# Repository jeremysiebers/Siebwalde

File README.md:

# Siebwalde-Source
Siebwalde project

This project is dedicated for the ModelTrain Yard of Siebwalde: 
- https://www.youtube.com/c/SiebersOrg
- http://www.siebers.org/index.html
- https://www.youtube.com/channel/UCRJYaY8l7wVBrel3Bn0nD2Q/videos?view_as=subscriber

It contains sources for:

Windows Application (C#)

- Siebwalde_Application     --> C# main App to control all

uCOntrollers (C):

- FiddleYard                --> Embedded ethernet uController, controlling the FiddleYard PIC18F97j60

- ServoController.X         --> Embedded uController for RC servo driving

- TrackAmplifier4.X         --> development of track amplifiers; 1 PIC per amplifier (final setup with PIC18F25K40)(PetitModbus)*

- TrackBackplane2.X         --> development of track backplane slave; track amplifier slave select slave for initialization (final setup with PIC18F25K40)(PetitModbus)*

- TrackController5.X        --> development of track controller; PIC32MZ2048EFH144 Ethernet Target + ModBus Master(build upon PetitModbus)*

PCB Files (KiCad):

- KiCad                     --> All Siebwalde related KiCad (PCB) designs

*PetitModbus derived from https://github.com/FxDev/PetitModbus

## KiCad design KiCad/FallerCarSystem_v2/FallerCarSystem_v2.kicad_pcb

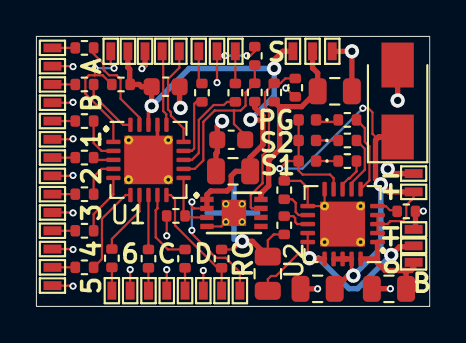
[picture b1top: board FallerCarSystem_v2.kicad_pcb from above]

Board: 2 copper layers, 21.8 x 15.0 mm, 77 parts (0 on the bottom side), 46 nets.

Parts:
C1, C2: 0.1uF; C_0603_1608Metric
C3, C5, C6, C7: 4.7uF; C_0805_2012Metric
C4: 10uF; C_0805_2012Metric
D1: SMAJ5.0A/AC; D_SMA
D2, D3, D4: LED; LED_0402_1005Metric
J1, J2, J3, J4, J5, J6, J7, J8, J9, J10, J11, J12, J13, J14, J15, J16, J17, J18, J19, J20, J21, J22, J23, J24, J25, J26, J27, J28, J29, J30, J31, J32, J33, J34, J35, J36, J37, J38: Conn_01x01_Male; TestPoint_Pad_0.5x1.0mm
R1, R2, R9, R15: 4.7k; R_0402_1005Metric
R3: 4k7; R_0402_1005Metric
R4: 18k; R_0402_1005Metric
R5, R6: 200E; R_0402_1005Metric
R7: 220k; R_0402_1005Metric
R8: 10k; R_0402_1005Metric
R10: 47k; R_0402_1005Metric
R11: 22k; R_0402_1005Metric
R12, R13, R14, R16, R17, R18, R19, R20, R21, R22, R23, R24, R25: 470E; R_0402_1005Metric
U1: PIC16F15345-I_GZ-MCU_Microchip_PIC16; QFN-20-1EP_4x4mm_P0.5mm_EP2.7x2.7mm_ThermalVias
U2: MCP73871-2AA; QFN-20-1EP_4x4mm_P0.5mm_EP2.5x2.5mm_ThermalVias
U3: MCP1725-ADJE_MC_DFN-8-Regulator_Linear; DFN-8-1EP_3x2mm_P0.5mm_EP1.36x1.46mm_ThermalVias

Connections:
+3V8: C1.1, C3.1, J5.1, J12.1, J13.1, R1.2, R3.2, U1.18, U3.1, U3.2
+5V: C4.1, D1.1, D2.2, D3.2, D4.2, J15.1, U2.2, U2.3, U2.4, U2.9, U2.17, U2.18, U2.19
/PG: R12.1, U2.6
/STAT1: R13.1, U2.8
/STAT2: R14.1, U2.7
BATT: C6.1, J17.1, U2.14, U2.15, U2.16
EnMOT: R9.2, U1.11, U3.3
GND: C1.2, C2.2, C3.2, C4.2, C5.2, C6.2, C7.2, D1.2, J3.1, J6.1, J10.1, J16.1, J18.1, J20.1, J22.1, J24.1, J26.1, J28.1, J30.1, J32.1, J34.1, J36.1, J38.1, R2.1, R4.1, R7.1, R8.1, R9.1, R11.1, R15.1, U1.17, U1.21, U2.10, U2.11, U2.21, U3.4, U3.9
ICSPCLK: J8.1, U1.15
ICSPDATA: J7.1, U1.16
LEDA: R23.2, U1.19
LEDB: R22.2, U1.20
LEDC: R25.2, U1.8
LEDD: R24.2, U1.9
MOTOR+: C5.1, J9.1, R10.2, U3.8
unnamed: D2.1, R12.2
unnamed: D3.1, R13.2
unnamed: D4.1, R14.2
unnamed: J19.1, R16.1
unnamed: J21.1, R17.1
unnamed: J23.1, R18.1
unnamed: J25.1, R19.1
unnamed: J27.1, R20.1
unnamed: J29.1, R21.1
unnamed: J31.1, R22.1
unnamed: J33.1, R23.1
unnamed: J35.1, R24.1
unnamed: J37.1, R25.1
unnamed: R4.2, U2.13
unnamed: R5.2, U1.13
unnamed: R6.2, U1.14
unnamed: R7.2, U2.12
unnamed: R8.2, U2.5
unnamed: R10.1, R11.2, U3.7
PWM1: R16.2, U1.2
PWM2: R17.2, U1.3
PWM3: R18.2, U1.4
PWM4: R19.2, U1.5
PWM5: R20.2, U1.6
PWM6: R21.2, U1.7
RCS_IN: J14.1, R15.2, U1.10
SWONOFF_OUT: C7.1, J11.1, U2.1, U2.20
UART_RX: J2.1, R6.1
UART_TX: J1.1, R5.1
Vbatt: C2.1, R1.1, R2.2, U1.12
Vpp: J4.1, R3.1, U1.1

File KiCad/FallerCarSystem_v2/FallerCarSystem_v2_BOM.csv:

Comment,Designator,Footprint
0.1uF,"C1, C2",Capacitor_SMD:C_0603_1608Metric
4.7uF,"C3, C5, C6, C7",Capacitor_SMD:C_0805_2012Metric
10uF,C4,Capacitor_SMD:C_0805_2012Metric
SMAJ5.0A/AC,D1,Diode_SMD:D_SMA
Everlight Elec 16-213SYGC/S530-E3/TR8,"D2, D4",LED_SMD:LED_0402_1005Metric
Everlight Elec 16-213/SDRC/S530-A3/TR8,D3,LED_SMD:LED_0402_1005Metric
4.7k,"R1, R2, R3, R9, R15",Resistor_SMD:R_0402_1005Metric
18k,R4,Resistor_SMD:R_0402_1005Metric
200,"R5, R6",Resistor_SMD:R_0402_1005Metric
220k,R7,Resistor_SMD:R_0402_1005Metric
10k,R8,Resistor_SMD:R_0402_1005Metric
47k,R10,Resistor_SMD:R_0402_1005Metric
22k,R11,Resistor_SMD:R_0402_1005Metric
470,"R12, R13, R14",Resistor_SMD:R_0402_1005Metric
150,"R16, R17, R18, R19, R20, R21, R22, R23, R24, R25",Resistor_SMD:R_0402_1005Metric
PIC16F15345-I_GZ-MCU_Microchip_PIC16_UQFN_20_4x4,U1,Package_DFN_QFN:QFN-20-1EP_4x4mm_P0.5mm_EP2.7x2.7mm_ThermalVias
MCP73871-2AA_VQFN_20_4x4,U2,Package_DFN_QFN:QFN-20-1EP_4x4mm_P0.5mm_EP2.5x2.5mm_ThermalVias
MCP1725-ADJE_MC_DFN-8-Regulator_Linear,U3,Package_DFN_QFN:DFN-8-1EP_3x2mm_P0.5mm_EP1.36x1.46mm_ThermalVias

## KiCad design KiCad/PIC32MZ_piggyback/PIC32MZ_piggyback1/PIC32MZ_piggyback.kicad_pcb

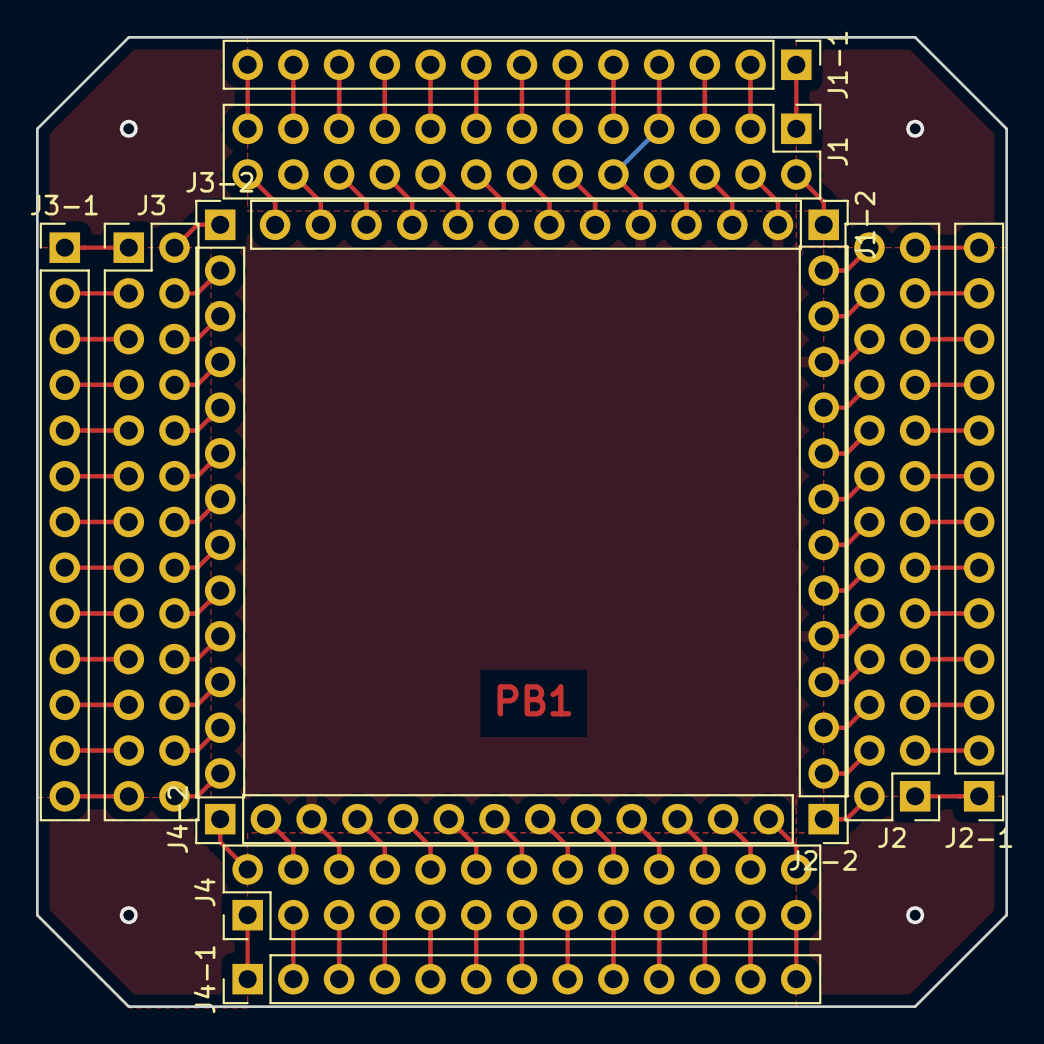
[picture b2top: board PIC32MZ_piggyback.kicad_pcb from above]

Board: 2 copper layers, 53.8 x 53.8 mm, 12 parts (0 on the bottom side), 84 nets.

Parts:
J1, J2, J3, J4: Conn_02x13_Odd_Even; PinHeader_2x13_P2.54mm_Vertical
J1-1, J1-2, J2-1, J2-2, J3-1, J3-2, J4-1, J4-2: Conn_01x13_Male; PinHeader_1x13_P2.54mm_Vertical

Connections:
/GND: J1.4, J1.7, J1.10, J1-1.4, J1-2.2, J1-2.5, J2.10, J2.15, J2.22, J2-1.8, J2-2.5, J2-2.11, J3.15, J3-1.8, J4.6, J4.11, J4.15, J4-1.6, J4-1.8, J4-2.3
/LED1: J3.3, J3-1.2, J4.9, J4-1.5
/LED2: J3.5, J3-1.3, J4.10, J4-2.5
/MCLR: J3.13, J3-1.7
/MCU_MISO: J4.7, J4-1.4
/MCU_MOSI: J4.18, J4-2.9
/MCU_SCK: J4.16, J4-2.8
/RA0: J1.17, J1-1.9
/RA1: J3.18, J3-2.9
/RA2: J4.13, J4-1.7
/RA3: J4.20, J4-2.10
/RA4: J4.19, J4-1.10
/RA5: J4.22, J4-2.11
/RA9: J3.7, J3-1.4
/RA10: J3.12, J3-2.6
/RA14: J4.21, J4-1.11
/RA15: J4.24, J4-2.12
/RB0: J1.25, J1-1.13
/RB1: J1.26, J1-2.13
/RB2: J1.23, J1-1.12
/RB3: J1.24, J1-2.12
/RB4: J1.21, J1-1.11
/RB5: J1.22, J1-2.11
/RB6: J2.17, J2-1.9
/RB7: J2.7, J2-1.4
/RB8: J3.9, J3-1.5
/RB9: J3.14, J3-2.7
/RB10: J3.11, J3-1.6
/RB11: J3.16, J3-2.8
/RB12: J3.19, J3-1.10
/RB13: J3.22, J3-2.11
/RB14: J3.21, J3-1.11
/RB15: J3.24, J3-2.12
/RC1: J1.8, J1-2.4
/RC2: J1.9, J1-1.5
/RC3: J1.12, J1-2.6
/RC4: J1.13, J1-1.7
/RD0: J4.25, J4-1.13
/RD1: J2.1, J2-1.1
/RD2: J2.2, J2-2.1
/RD3: J2.3, J2-1.2
/RD4: J2.11, J2-1.6
/RD5: J2.8, J2-2.4
/RD7: J2.14, J2-2.7
/RD9: J4.26, J4-2.13
/RD10: J4.23, J4-1.12
/RD12: J2.5, J2-1.3
/RD13: J2.4, J2-2.2
/RD14: J3.23, J3-1.12
/RE0: J2.18, J2-2.9
/RE2: J2.21, J2-1.11
/RE3: J2.26, J2-2.13
/RE7: J1.5, J1-1.3
/RE8: J1.20, J1-2.10
/RE9: J1.19, J1-1.10
/RF0: J2.16, J2-2.8
/RF1: J2.13, J2-1.7
/RF3: J4.14, J4-2.7
/RF4: J3.25, J3-1.13
/RF5: J3.26, J3-2.13
/RF12: J3.20, J3-2.10
/RG6: J1.14, J1-2.7
/RG7: J1.15, J1-1.8
/RG8: J1.16, J1-2.8
/RG9: J1.18, J1-2.9
/RG12: J2.19, J2-1.10
/RG14: J2.20, J2-2.10
/RXN: J2.23, J2-1.12
/RXP: J2.24, J2-2.12
/TXN: J1.2, J1-2.1
/TXP: J1.3, J1-1.2
/VCC: J1.1, J1.6, J1.11, J1-1.1, J1-1.6, J1-2.3, J2.9, J2.12, J2.25, J2-1.5, J2-1.13, J2-2.6, J3.17, J3-1.9, J4.4, J4.5, J4.12, J4-1.3, J4-2.2, J4-2.6
unnamed: J2.6, J2-2.3
unnamed: J3.1, J3-1.1
unnamed: J3.2, J3-2.1
unnamed: J3.4, J3-2.2
unnamed: J3.6, J3-2.3
unnamed: J3.8, J3-2.4
unnamed: J3.10, J3-2.5
unnamed: J4.1, J4-1.1
unnamed: J4.3, J4-1.2
unnamed: J4.17, J4-1.9
unnamed: J4.2, J4-2.1
unnamed: J4.8, J4-2.4

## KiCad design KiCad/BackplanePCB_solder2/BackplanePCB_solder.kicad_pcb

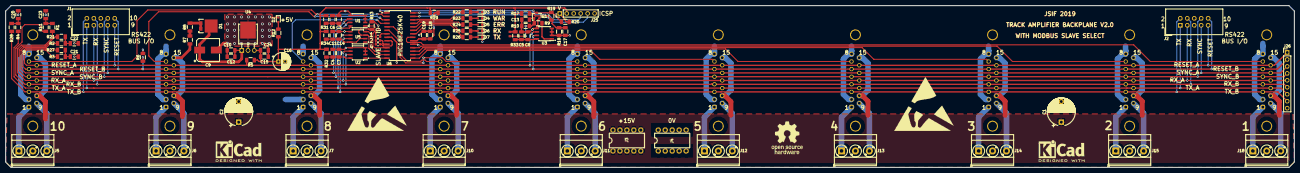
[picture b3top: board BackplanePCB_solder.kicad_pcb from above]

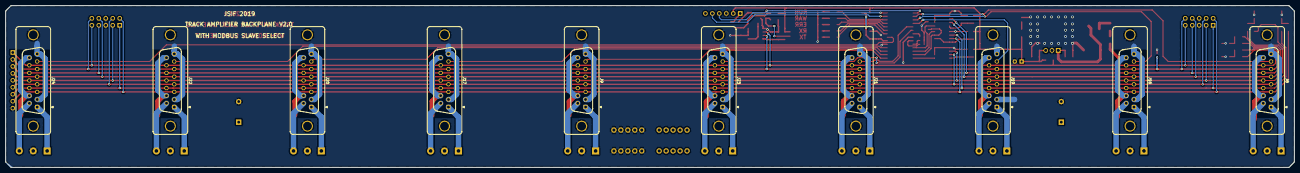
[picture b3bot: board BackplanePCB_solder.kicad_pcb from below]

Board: 2 copper layers, 470.0 x 59.0 mm, 98 parts (10 on the bottom side), 78 nets.

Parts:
C1, C2: 470u; CP_Radial_D10.0mm_P7.50mm
C3, C4, C5, C10, C11, C18, C24: 4.7u; C_1206_3216Metric
C6, C7, C8, C12, C13, C14, C15, C17, C19, C20, C21, C22, C23: 100n; C_1206_3216Metric
C9: 220u; CP_Elec_8x10.5
C16: 220u; CP_Radial_D6.3mm_P2.50mm
D1: D_Schottky_AAK; TO-277A
D2, D3: LED GR RUN; LED_0.8x0.8
D4: LED YE WAR; LED_0.8x0.8
D5: LED RD ERR; LED_0.8x0.8
D6: LED GR RX; LED_0.8x0.8
D7: LED GR TX; LED_0.8x0.8
J1, J2: Conn_02x05_Odd_Even; IDC-Header_2x05_P2.54mm_Vertical
J3: PowerBug+15V; DIP-10_W7.62mm
J4: PowerBug_GND; DIP-10_W7.62mm
J5, J6, J7, J10, J11, J12, J13, J14, J15, J18: Conn_01x03; TerminalBlock_Phoenix_MKDS-3-3-5.08_1x03_P5.08mm_Horizontal
J8, J9, J16, J17, J19, J20, J21, J22, J23, J24: DB15_Female_MountingHoles; DSUB-15_Female_Vertical_P2.77x2.84mm_MountingHoles
J25: Conn_01x06; PinHeader_1x06_P2.54mm_Vertical
J26: Conn_01x09; PinHeader_1x09_P2.54mm_Vertical
Q1: NTR5103NT1G; SOT-23
R1, R2, R3, R4, R11, R21, R27, R28: 60E; R_1206_3216Metric
R5, R6: 2k; R_1206_3216Metric
R7, R8: 10E; R_1206_3216Metric
R9, R13: 1k; R_1206_3216Metric
R10, R17: 10k; R_1206_3216Metric
R12, R22, R23, R24, R25, R26: 300E; R_1206_3216Metric
R14, R15, R16: R; R_0603_1608Metric
R18: 110k; R_1206_3216Metric
R19, R20: 470; R_1206_3216Metric
R29, R31, R32, R33, R34: 0E; R_1206_3216Metric
R30: NP; R_0603_1608Metric
U1, U2, U3, U5: ST485EBDR; SOIC-8_3.9x4.9mm_P1.27mm
U4: L78M05CDT-1-TO-251-3; TO-251-3-1EP_Horizontal_TabDown
U6: PIC16F18854-SO; SOIC-28W_7.5x17.9mm_P1.27mm

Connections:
+5V: C15.1, C16.1, C24.1, J25.2, R5.1, R12.1, R17.2, R29.1, R30.1, R31.1, R32.1, R33.1, R34.1, U4.3
+15V: C1.1, C2.1, J3.1, J3.2, J3.3, J3.4, J3.5, J3.6, J3.7, J3.8, J3.9, J3.10, J8.10, J8.15, J9.10, J9.15, J16.10, J16.15, J17.10, J17.15, J19.10, J19.15, J20.10, J20.15, J21.10, J21.15, J22.10, J22.15, J23.10, J23.15, J24.10, J24.15, R7.1
/PWMO1_1: J5.3, J8.9
/PWMO1_2: J6.3, J16.9
/PWMO1_3: J7.3, J19.9
/PWMO1_4: J10.3, J21.9
/PWMO1_5: J11.3, J23.9
/PWMO1_6: J9.9, J12.3
/PWMO1_7: J13.3, J17.9
/PWMO1_8: J14.3, J20.9
/PWMO1_9: J15.3, J22.9
/PWMO1_10: J18.3, J24.9
/PWMO2_1: J5.1, J8.1
/PWMO2_2: J6.1, J16.1
/PWMO2_3: J7.1, J19.1
/PWMO2_4: J10.1, J21.1
/PWMO2_5: J11.1, J23.1
/PWMO2_6: J9.1, J12.1
/PWMO2_7: J13.1, J17.1
/PWMO2_8: J14.1, J20.1
/PWMO2_9: J15.1, J22.1
/PWMO2_10: J18.1, J24.1
GND: C1.2, C2.2, C3.2, C4.2, C5.2, C6.2, C7.2, C8.2, C9.2, C10.2, C11.2, C12.2, C13.2, C14.2, C15.2, C16.2, C17.2, C18.2, C19.2, C20.2, C21.2, C22.2, C23.2, C24.2, D2.1, D3.1, D4.1, D5.1, D6.1, D7.1, J1.5, J1.6, J2.5, J2.6, J4.1, J4.2, J4.3, J4.4, J4.5, J4.6, J4.7, J4.8, J4.9, J4.10, J5.2, J6.2, J7.2, J8.0, J8.2, J8.8, J9.0, J9.2, J9.8, J10.2, J11.2, J12.2, J13.2, J14.2, J15.2, J16.0, J16.2, J16.8, J17.0, J17.2, J17.8, J18.2, J19.0, J19.2, J19.8, J20.0, J20.2, J20.8, J21.0, J21.2, J21.8, J22.0, J22.2, J22.8, J23.0, J23.2, J23.8, J24.0, J24.2, J24.8, J25.3, J26.9, Q1.2, R6.1, R10.2, R13.1, R14.2, R15.2, R16.2, R18.1, U1.2, U1.3, U1.4, U1.5, U2.2, U2.3, U2.4, U2.5, U3.2, U3.3, U3.4, U3.5, U4.2, U4.4, U5.5, U6.8, U6.19
ICSPCLK: J25.5, U6.27
ICSPDAT: J25.4, U6.28
ID_1: J24.7, U6.21
ID_2: J22.7, U6.18
ID_3: J20.7, U6.17
ID_4: J17.7, U6.16
ID_5: J9.7, U6.15
ID_6: J23.7, U6.6
ID_7: J21.7, U6.5
ID_8: J19.7, U6.4
ID_9: J16.7, U6.3
ID_10: J8.7, U6.2
unnamed: C3.1, C6.1, R31.2, U1.8
unnamed: C4.1, C7.1, R32.2, U2.8
unnamed: C5.1, C8.1, R33.2, U3.8
unnamed: C9.1, C10.1, C12.1, D1.3, U4.1
unnamed: C11.1, C14.1, R34.2, U5.2, U5.8
unnamed: C13.1, Q1.1, R9.2, R10.1, R30.2
unnamed: C17.1, R17.1, R18.2, R19.1
unnamed: C18.1, C19.1, R29.2, U6.20
unnamed: C20.1, R4.1, R28.2
unnamed: C21.1, R3.1, R27.2
unnamed: C22.1, R2.1, R21.2
unnamed: C23.1, R1.1, R11.2
unnamed: D1.1, D1.2, R8.2
unnamed: D2.2, R12.2
unnamed: D3.2, R22.2
unnamed: D4.2, R23.2
unnamed: D5.2, R24.2
unnamed: D6.2, R25.2
unnamed: D7.2, R26.2
unnamed: R7.2, R8.1
unnamed: R9.1, U3.1
unnamed: R14.1, U6.7
unnamed: R15.1, U6.10
unnamed: R16.1, U6.9
unnamed: R22.1, U6.26
unnamed: R23.1, U6.25
unnamed: R24.1, U6.24
unnamed: R25.1, U6.23
unnamed: R26.1, U6.22
RESET_A: J1.9, J2.9, J8.14, J9.14, J16.14, J17.14, J19.14, J20.14, J21.14, J22.14, J23.14, J24.14, J26.1, R3.2, R5.2, U3.6
RESET_B: J1.10, J2.10, J8.6, J9.6, J16.6, J17.6, J19.6, J20.6, J21.6, J22.6, J23.6, J24.6, J26.2, R6.2, R27.1, U3.7
RST: Q1.3, R19.2, R20.1, U6.1
RX: U2.1, U6.14
RX_A: J1.3, J2.3, J8.12, J9.12, J16.12, J17.12, J19.12, J20.12, J21.12, J22.12, J23.12, J24.12, J26.5, R1.2, U2.6
RX_B: J1.4, J2.4, J8.4, J9.4, J16.4, J17.4, J19.4, J20.4, J21.4, J22.4, J23.4, J24.4, J26.6, R11.1, U2.7
SYNC: U1.1, U6.11
SYNC_A: J1.7, J2.7, J8.13, J9.13, J16.13, J17.13, J19.13, J20.13, J21.13, J22.13, J23.13, J24.13, J26.3, R2.2, U1.6
SYNC_B: J1.8, J2.8, J8.5, J9.5, J16.5, J17.5, J19.5, J20.5, J21.5, J22.5, J23.5, J24.5, J26.4, R21.1, U1.7
TX: U5.4, U6.12
TX_A: J1.1, J2.1, J8.11, J9.11, J16.11, J17.11, J19.11, J20.11, J21.11, J22.11, J23.11, J24.11, J26.7, R4.2, U5.6
TX_B: J1.2, J2.2, J8.3, J9.3, J16.3, J17.3, J19.3, J20.3, J21.3, J22.3, J23.3, J24.3, J26.8, R28.1, U5.7
TX_ENA: R13.2, U5.3, U6.13
VPP: J25.1, R20.2

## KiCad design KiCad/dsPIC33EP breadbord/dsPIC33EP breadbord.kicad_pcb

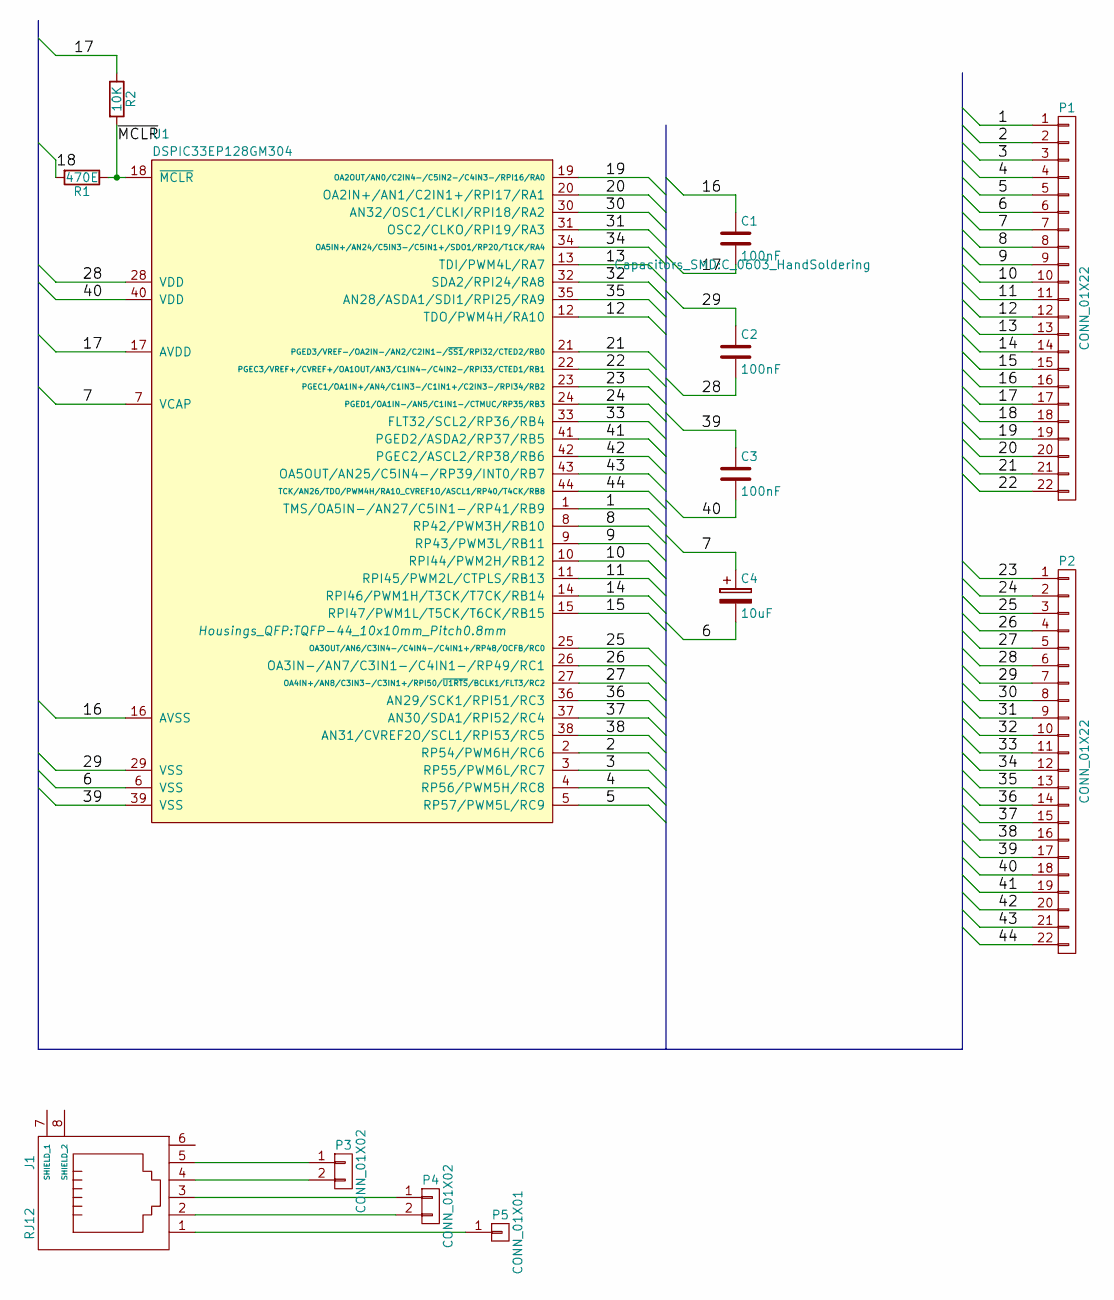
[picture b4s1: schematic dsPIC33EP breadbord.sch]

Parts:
C1, C2, C3: 100nF; C_0603_HandSoldering
C4: 10uF; TantalC_SizeA_EIA-3216_HandSoldering
J1: RJ12; RJ12_E
P1, P2: CONN_01X22; Pin_Header_Straight_1x22
P3, P4: CONN_01X02; Pin_Header_Straight_1x02
P5: CONN_01X01; Pin_Header_Straight_1x01
R1: 470E; R_0603_HandSoldering
R2: 10K; R_0603_HandSoldering
U1: DSPIC33EP128GM304; TQFP-44_10x10mm_Pitch0.8mm

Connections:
/1: P1.1, U1.1 (TMS/OA5IN-/AN27/C5IN1-/RP41/RB9)
/2: P1.2, U1.2 (RP54/PWM6H/RC6)
/3: P1.3, U1.3 (RP55/PWM6L/RC7)
/4: P1.4, U1.4 (RP56/PWM5H/RC8)
/5: P1.5, U1.5 (RP57/PWM5L/RC9)
/6: C4.2, P1.6, U1.6 (VSS)
/7: C4.1, P1.7, U1.7 (VCAP)
/8: P1.8, U1.8 (RP42/PWM3H/RB10)
/9: P1.9, U1.9 (RP43/PWM3L/RB11)
/10: P1.10, U1.10 (RPI44/PWM2H/RB12)
/11: P1.11, U1.11 (RPI45/PWM2L/CTPLS/RB13)
/12: P1.12, U1.12 (TDO/PWM4H/RA10)
/13: P1.13, U1.13 (TDI/PWM4L/RA7)
/14: P1.14, U1.14 (RPI46/PWM1H/T3CK/T7CK/RB14)
/15: P1.15, U1.15 (RPI47/PWM1L/T5CK/T6CK/RB15)
/16: C1.1, P1.16, U1.16 (AVSS)
/17: C1.2, P1.17, R2.1, U1.17 (AVDD)
/18: P1.18, R1.2
/19: P1.19, U1.19 (OA2OUT/AN0/C2IN4-/C5IN2-/C4IN3-/RPI16/R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)
/20: P1.20, U1.20 (OA2IN+/AN1/C2IN1+/RPI17/RA1)
/21: P1.21, U1.21 (PGED3/VREF-/OA2IN-/AN2/C2IN1-/~SS1~/RPI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)
/22: P1.22, U1.22 (PGEC3/VREF+/CVREF+/OA1OUT/AN3/C1IN4-/C4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)
/23: P2.1, U1.23 (PGEC1/OA1IN+/AN4/C1IN3-/C1IN1+/C2IN3-/R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)
/24: P2.2, U1.24 (PGED1/OA1IN-/AN5/C1IN1-/CTMUC/RP35/RB3)
/25: P2.3, U1.25 (OA3OUT/AN6/C3IN4-/C4IN4-/C4IN1+/RP48/OC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)
/26: P2.4, U1.26 (OA3IN-/AN7/C3IN1-/C4IN1-/RP49/RC1)
/27: P2.5, U1.27 (OA4IN+/AN8/C3IN3-/C3IN1+/RPI50/~U1RTS~/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)
/28: C2.2, P2.6, U1.28 (VDD)
/29: C2.1, P2.7, U1.29 (VSS)
/30: P2.8, U1.30 (AN32/OSC1/CLKI/RPI18/RA2)
/31: P2.9, U1.31 (OSC2/CLKO/RPI19/RA3)
/32: P2.10, U1.32 (SDA2/RPI24/RA8)
/33: P2.11, U1.33 (FLT32/SCL2/RP36/RB4)
/34: P2.12, U1.34 (OA5IN+/AN24/C5IN3-/C5IN1+/SDO1/RP20/T1C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)
/35: P2.13, U1.35 (AN28/ASDA1/SDI1/RPI25/RA9)
/36: P2.14, U1.36 (AN29/SCK1/RPI51/RC3)
/37: P2.15, U1.37 (AN30/SDA1/RPI52/RC4)
/38: P2.16, U1.38 (AN31/CVREF2O/SCL1/RPI53/RC5)
/39: C3.1, P2.17, U1.39 (VSS)
/40: C3.2, P2.18, U1.40 (VDD)
/41: P2.19, U1.41 (PGED2/ASDA2/RP37/RB5)
/42: P2.20, U1.42 (PGEC2/ASCL2/RP38/RB6)
/43: P2.21, U1.43 (OA5OUT/AN25/C5IN4-/RP39/INT0/RB7)
/44: P2.22, U1.44 (TCK/AN26/TDO/PWM4H/RA10_CVREF1O/ASCL1/R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)
/~MCLR~: R1.1, R2.2, U1.18 (~MCLR)
unnamed: J1.1, P5.1
unnamed: J1.2, P4.2
unnamed: J1.3, P4.1
unnamed: J1.4, P3.2
unnamed: J1.5, P3.1

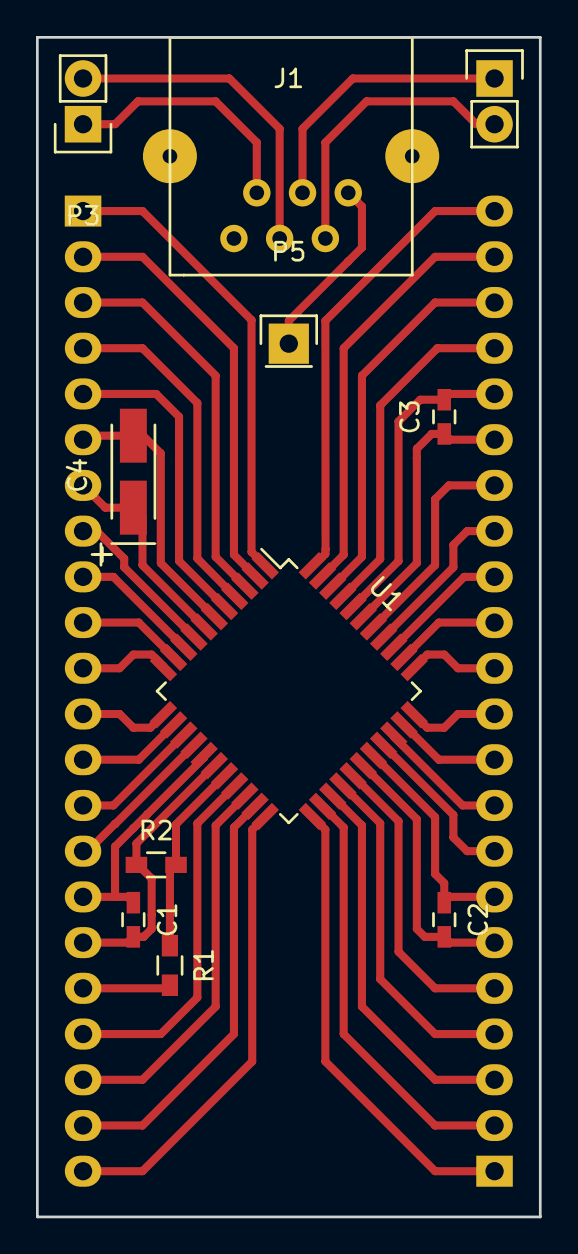
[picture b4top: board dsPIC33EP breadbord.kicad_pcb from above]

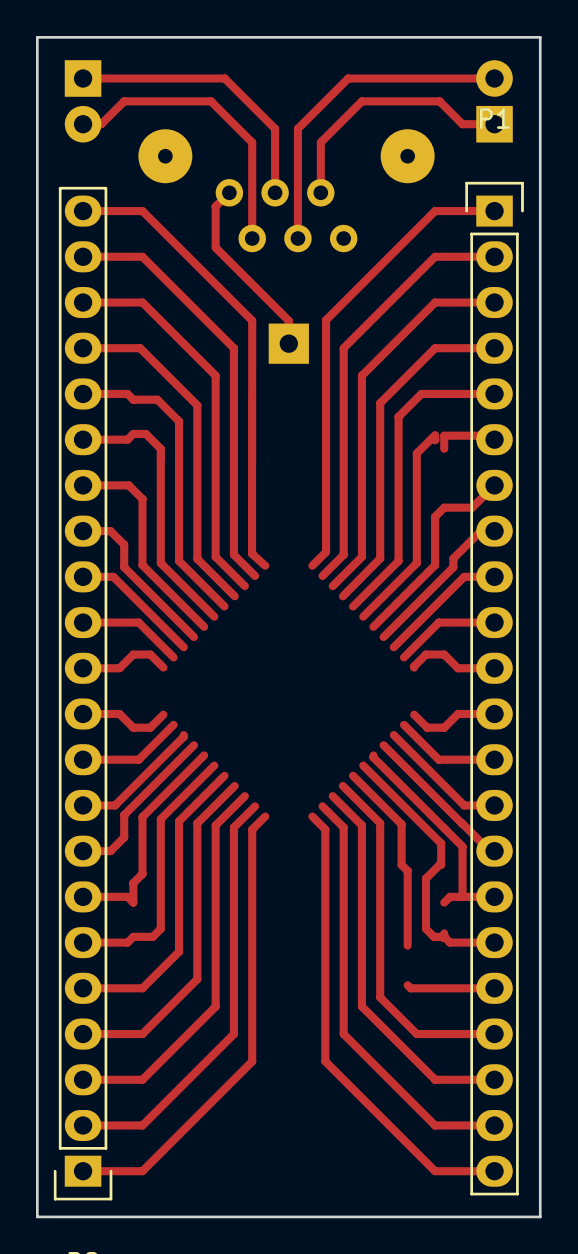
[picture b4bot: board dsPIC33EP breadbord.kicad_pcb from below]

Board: 2 copper layers, 27.9 x 65.5 mm, 13 parts (2 on the bottom side), 50 nets.

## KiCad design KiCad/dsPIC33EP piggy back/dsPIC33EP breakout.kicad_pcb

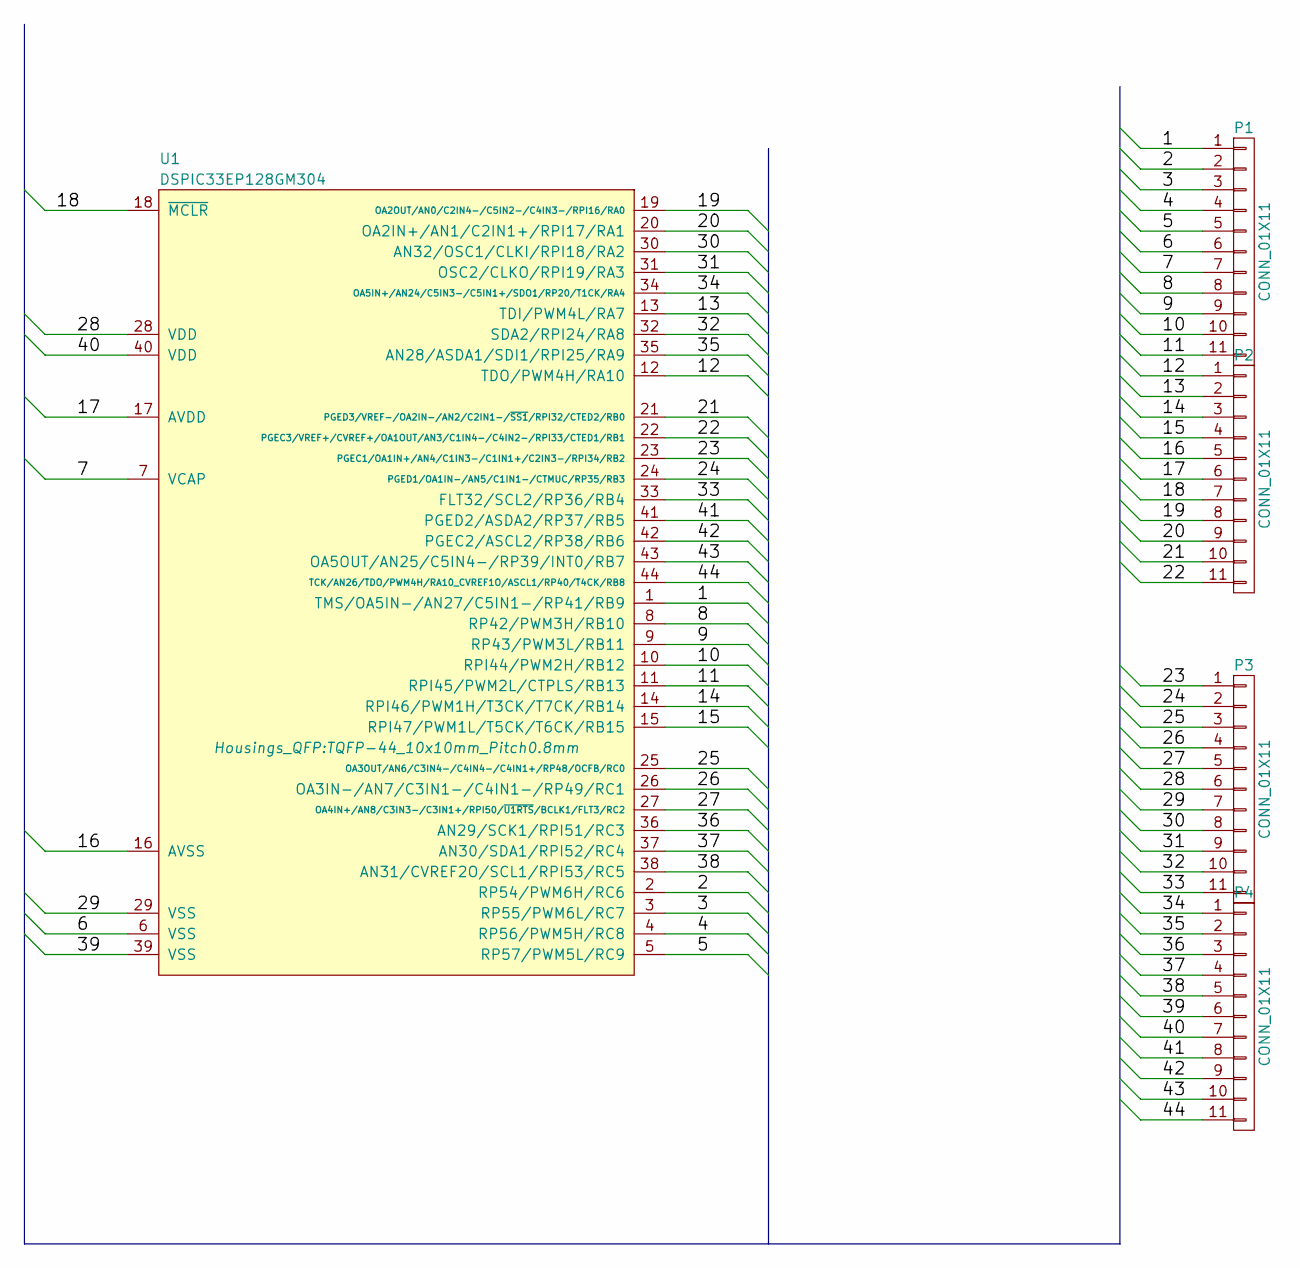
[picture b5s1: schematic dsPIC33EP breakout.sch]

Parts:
P1, P2, P3, P4: CONN_01X11; Pin_Header_Straight_1x11
U1: DSPIC33EP128GM304; TQFP-44_10x10mm_Pitch0.8mm

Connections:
/1: P1.1, U1.1 (TMS/OA5IN-/AN27/C5IN1-/RP41/RB9)
/2: P1.2, U1.2 (RP54/PWM6H/RC6)
/3: P1.3, U1.3 (RP55/PWM6L/RC7)
/4: P1.4, U1.4 (RP56/PWM5H/RC8)
/5: P1.5, U1.5 (RP57/PWM5L/RC9)
/6: P1.6, U1.6 (VSS)
/7: P1.7, U1.7 (VCAP)
/8: P1.8, U1.8 (RP42/PWM3H/RB10)
/9: P1.9, U1.9 (RP43/PWM3L/RB11)
/10: P1.10, U1.10 (RPI44/PWM2H/RB12)
/11: P1.11, U1.11 (RPI45/PWM2L/CTPLS/RB13)
/12: P2.1, U1.12 (TDO/PWM4H/RA10)
/13: P2.2, U1.13 (TDI/PWM4L/RA7)
/14: P2.3, U1.14 (RPI46/PWM1H/T3CK/T7CK/RB14)
/15: P2.4, U1.15 (RPI47/PWM1L/T5CK/T6CK/RB15)
/16: P2.5, U1.16 (AVSS)
/17: P2.6, U1.17 (AVDD)
/18: P2.7, U1.18 (~MCLR)
/19: P2.8, U1.19 (OA2OUT/AN0/C2IN4-/C5IN2-/C4IN3-/RPI16/R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)
/20: P2.9, U1.20 (OA2IN+/AN1/C2IN1+/RPI17/RA1)
/21: P2.10, U1.21 (PGED3/VREF-/OA2IN-/AN2/C2IN1-/~SS1~/RPI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)
/22: P2.11, U1.22 (PGEC3/VREF+/CVREF+/OA1OUT/AN3/C1IN4-/C4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)
/23: P3.1, U1.23 (PGEC1/OA1IN+/AN4/C1IN3-/C1IN1+/C2IN3-/R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)
/24: P3.2, U1.24 (PGED1/OA1IN-/AN5/C1IN1-/CTMUC/RP35/RB3)
/25: P3.3, U1.25 (OA3OUT/AN6/C3IN4-/C4IN4-/C4IN1+/RP48/OC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)
/26: P3.4, U1.26 (OA3IN-/AN7/C3IN1-/C4IN1-/RP49/RC1)
/27: P3.5, U1.27 (OA4IN+/AN8/C3IN3-/C3IN1+/RPI50/~U1RTS~/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)
/28: P3.6, U1.28 (VDD)
/29: P3.7, U1.29 (VSS)
/30: P3.8, U1.30 (AN32/OSC1/CLKI/RPI18/RA2)
/31: P3.9, U1.31 (OSC2/CLKO/RPI19/RA3)
/32: P3.10, U1.32 (SDA2/RPI24/RA8)
/33: P3.11, U1.33 (FLT32/SCL2/RP36/RB4)
/34: P4.1, U1.34 (OA5IN+/AN24/C5IN3-/C5IN1+/SDO1/RP20/T1C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)
/35: P4.2, U1.35 (AN28/ASDA1/SDI1/RPI25/RA9)
/36: P4.3, U1.36 (AN29/SCK1/RPI51/RC3)
/37: P4.4, U1.37 (AN30/SDA1/RPI52/RC4)
/38: P4.5, U1.38 (AN31/CVREF2O/SCL1/RPI53/RC5)
/39: P4.6, U1.39 (VSS)
/40: P4.7, U1.40 (VDD)
/41: P4.8, U1.41 (PGED2/ASDA2/RP37/RB5)
/42: P4.9, U1.42 (PGEC2/ASCL2/RP38/RB6)
/43: P4.10, U1.43 (OA5OUT/AN25/C5IN4-/RP39/INT0/RB7)
/44: P4.11, U1.44 (TCK/AN26/TDO/PWM4H/RA10_CVREF1O/ASCL1/R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)

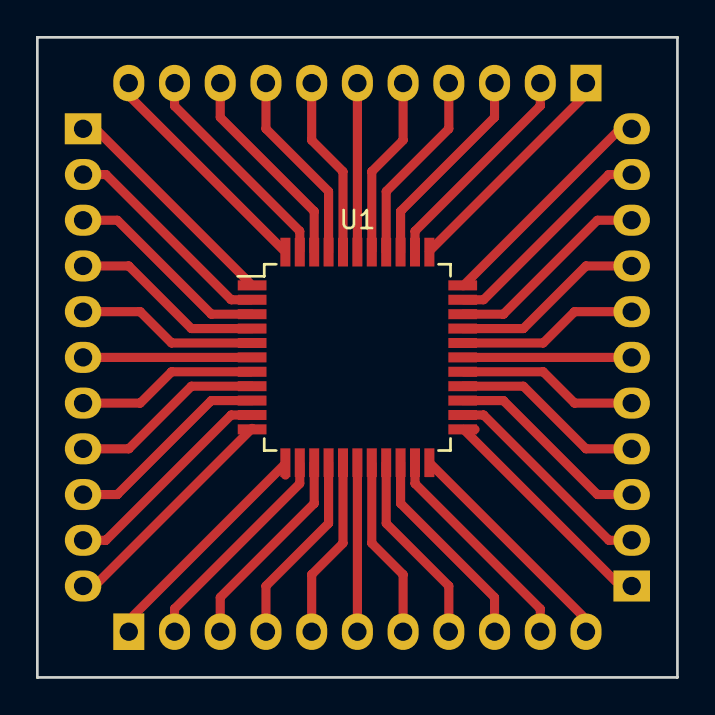
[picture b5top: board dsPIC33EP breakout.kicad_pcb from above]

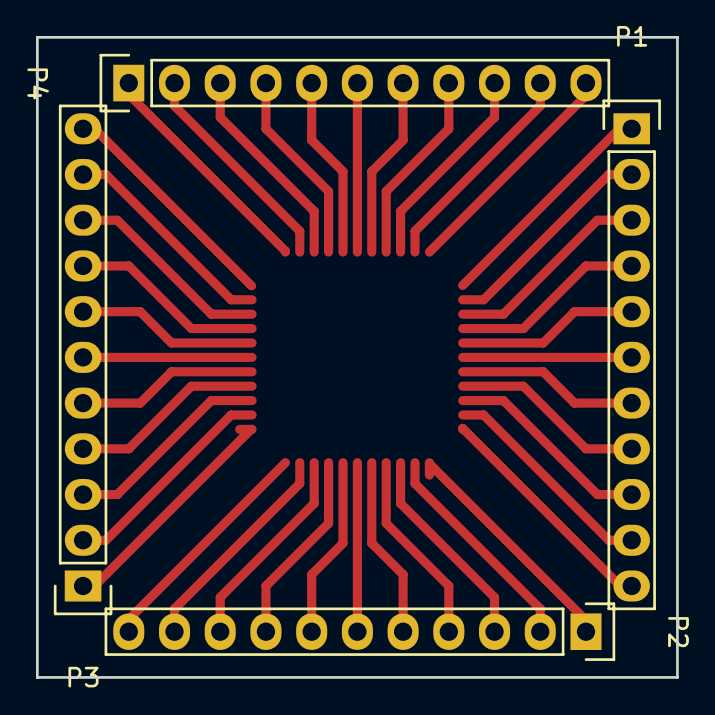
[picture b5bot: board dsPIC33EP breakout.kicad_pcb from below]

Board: 2 copper layers, 35.6 x 35.6 mm, 5 parts (4 on the bottom side), 44 nets.

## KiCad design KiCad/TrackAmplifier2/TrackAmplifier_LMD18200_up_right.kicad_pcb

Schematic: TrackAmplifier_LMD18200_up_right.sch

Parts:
C1, C2, C5, C8, C11, C12, C13, C19, C23, C26, C29, C30, C32, C34: 22u; C_1206_3216Metric
C3, C4, C7, C9, C10, C14, C15, C20, C21, C24, C25, C27, C31, C33, C35: 100n; C_1206_3216Metric
C6: 22u; CP_Axial_L21.0mm_D8.0mm_P28.00mm_Horizontal
C16: 100u; CP_Radial_D6.3mm_P2.50mm
C17, C18: 10n; C_1206_3216Metric
C22, C28: 1u; C_1206_3216Metric
D1, D2, D3, D4, D8: LED; LED_1206_3216Metric
D5, D6, D7: 1n4148; D_1206_3216Metric
FL1, FL2: EMI_Filter_CMode; Choke_EPCOS_B82722-A2302-N1-22.3x22.7mm
J1: DB15_Male_MountingHoles; DSUB-15_Male_Horizontal_P2.77x2.84mm_EdgePinOffset4.94mm_Ho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
J2: Conn_01x06; PinHeader_1x06_P2.54mm_Horizontal
MK1: Mounting_Hole; MountingHole_3.7mm_Pad_Via
Q1: 2N7002; SOT-23
R1, R2, R3, R5, R9, R10, R11, R12, R13, R15, R19, R20, R21, R22, R34, R37: 10E; R_1206_3216Metric
R4, R6, R7, R14: 4K7; R_1206_3216Metric
R8, R18, R23: 100E; R_1206_3216Metric
R16, R17, R38, R39: 0.2E; R_Axial_DIN0411_L9.9mm_D3.6mm_P12.70mm_Horizontal
R24: 3K3; R_1206_3216Metric
R25, R30, R33: 1K; R_1206_3216Metric
R26, R27, R28, R29, R35: 330E; R_1206_3216Metric
R31: 100K; R_1206_3216Metric
R32, R36: 10K; R_1206_3216Metric
U1, U2, U5, U6: ST485EBDR; SOIC-8_3.9x4.9mm_P1.27mm
U3: LM78M05_TO252; TO-252-2
U4: LMD18200; TO-220-11_20.02x17.50mm_P3.4x5.08mm_StaggerOdd_Lead8.45mm_T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
U7, U8: INA326; MSOP-8_3x3mm_P0.65mm
U9: PIC16F18854-SO; SOIC-28W_7.5x17.9mm_P1.27mm
U10: REF3025; SOT-23
U11: LM35-LP; TO-92

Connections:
+5V: C10.2, C13.2, C16.1, D5.1, J2.2, R1.2, R2.2, R4.2, R9.2, R10.2, R11.2, R12.1, R19.1, R22.1, R32.1, R33.1, R34.1, U3.3
+15V: C5.2, C7.2, R5.2, U3.1
BMF: C22.2, R18.1, U9.4
BRK: R4.1, U4.4, U9.16
CSEN: R24.2, R25.1, U4.8
CSEN_FLT: C29.2, R25.2, U9.21
DIR: R7.2, U4.3, U9.15
GND: C1.1, C2.1, C3.1, C4.1, C5.1, C6.2, C7.1, C8.1, C9.1, C10.1, C11.1, C12.1, C13.1, C14.1, C15.1, C16.2, C19.1, C20.1, C21.1, C22.1, C23.1, C24.1, C25.1, C26.1, C27.1, C28.1, C29.1, C30.1, C31.1, C32.1, C33.1, C34.1, C35.1, D1.1, D2.1, D3.1, D4.1, D6.2, D8.1, FL2.2, J2.3, Q1.2 (S), R6.1, R7.1, R14.1, R24.1, R31.2, R36.2, U1.2, U1.3, U1.4, U1.5, U3.2, U4.7, U5.5, U6.2, U6.3, U6.4, U6.5, U7.4, U8.4, U9.8, U9.19, U10.3 (GND), U11.3
ICSPCLK: J2.5, U9.27
ICSPDAT: J2.4, U9.28
ID: D5.2, D6.1, R30.2, U9.6
ID_R: C30.2, J1.2, R30.1, R33.2
unnamed: C1.2, C3.2, R1.1, U1.8
unnamed: C2.2, C4.2, R2.1, U2.8
unnamed: C11.2, C14.2, R9.1, U5.2, U5.8
unnamed: C12.2, C15.2, R10.1, U6.8
unnamed: C17.1, U4.1
unnamed: C18.2, U4.11
unnamed: C19.2, C20.2, R12.2, U7.7
unnamed: C21.2, R15.2, U7.5
unnamed: C23.2, C24.2, R19.2, U8.7
unnamed: C25.2, R21.2, U8.5
unnamed: C26.2, C27.2, R22.2, U9.20
unnamed: C31.2, D7.2, R31.1, R32.2
unnamed: C32.2, C33.2, R34.2, U10.1 (IN)
unnamed: C34.2, C35.2, R11.1, U11.1
unnamed: D1.2, R26.2
unnamed: D2.2, R27.2
unnamed: D3.2, R28.2
unnamed: D4.2, R35.1
unnamed: D8.2, R29.2
unnamed: FL2.3, J1.1, J1.8
unnamed: Q1.1 (G), R8.2, R36.1
unnamed: R3.2, R5.1
unnamed: R8.1, U1.1
unnamed: R13.1, U7.1
unnamed: R13.2, U7.8
unnamed: R16.2, R38.1
unnamed: R17.2, R39.1
unnamed: R18.2, U7.6
unnamed: R20.1, U8.1
unnamed: R20.2, U8.8
unnamed: R23.2, U8.6
unnamed: R26.1, U9.26
unnamed: R27.1, U9.25
unnamed: R28.1, U9.24
unnamed: R29.1, U9.22
unnamed: R35.2, U9.23
unnamed: R37.1, U11.2
unnamed: U2.2, U2.3, U2.4, U2.5
OCC: C28.2, R23.1, U9.5
OCC1: C17.2, R16.1, R17.1, U4.2, U7.3, U8.3
OCC2: FL1.1, R38.2, R39.2, U8.2
PWM: R6.2, U4.5, U9.17
PWM2: C18.1, FL1.3, U4.10, U7.2
PWMO1: FL1.2, J1.14
PWMO2: FL1.4, J1.7
RST: D7.1, J2.1, Q1.3 (D), U9.1
RX: U6.1, U9.14
RX_A: J1.12, U6.6
RX_B: J1.5, U6.7
Reset_A: J1.10, U1.6
Reset_B: J1.3, U1.7
SYNC: U2.1, U9.11
Sync_A: J1.11 (P111), U2.6
Sync_B: J1.4, U2.7
TEMP: R37.2, U9.18
TX: U5.4, U9.12
TX_A: J1.6, U5.6
TX_B: J1.13, U5.7
TX_ENA: R14.2, U5.3, U9.13
VREF: R15.1, R21.1, U9.2, U9.3, U10.2 (OUT)
Vbus_flt: C6.1, C8.2, C9.2, U4.6
Vbus_flt+: FL2.4, R3.1

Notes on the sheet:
Default Drivers Open BRAKE = H PWM = L DIR = X
~MCLR~ Vil = 0.2V Vih = 0.7V LVP is possible, HVP only when "RESET" transceiver input A < B
Disconnected receiver inputs or idle bus will have RO high. Invert for uController reset
Resistor on backplane will determine ID voltage
377uA/A --> 4A meauring range 5V / (377^-6 x 4) --> 3K3
length pcb = 104.7mm width pcb = 52mm heart conn to far pcb edge = 35mm Connector heart distance = 75mm Connector plate = 39.3mm Space between connector plates = 35.4mm
http://nl.farnell.com/epcos/b82722a2202n001/filter-common-mode-choke-2-2mh/dp/1223076?ost=B82722A2202N001&scope=partnumberlookahead&exaMfpn=true&searchref=searchlookahead&ddkey=http%3Anl-NL%2FElement14_Netherlands%2Fw%2Fsearch
Package_TO_SOT_THT:TO-220-11_Horizontal_TabDown_StaggeredType1_Py2.54mm

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
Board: 2 copper layers, 99 parts (1 on the bottom side), 75 nets, no tracks yet.

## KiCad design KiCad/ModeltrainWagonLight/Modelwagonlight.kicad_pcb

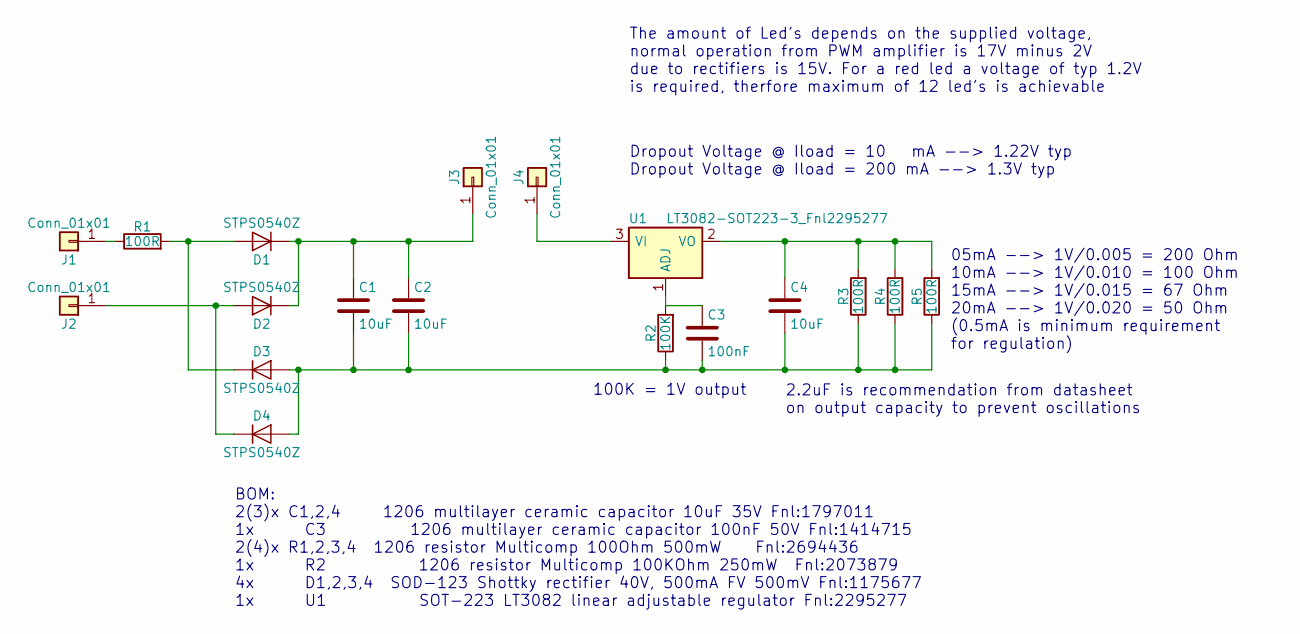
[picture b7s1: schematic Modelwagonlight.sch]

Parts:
C1, C2, C4: 10uF; C_1206_HandSoldering
C3: 100nF; C_1206_HandSoldering
D1, D2, D3, D4: STPS0540Z; D_SOD-123
J1, J2, J3, J4: Conn_01x01; Pin_Header_Straight_1x01_Pitch1.00mm
R1, R3, R4, R5: 100R; R_1206_HandSoldering
R2: 100K; R_1206_HandSoldering
U1: LT3082-SOT223-3_Fnl2295277; SOT-223-3_TabPin2

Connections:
unnamed: C1.1, C2.1, D1.1 (K), D2.1 (K), J3.1
unnamed: C1.2, C2.2, C3.2, C4.2, D3.2 (A), D4.2 (A), R2.1, R3.1, R4.1, R5.1
unnamed: C3.1, R2.2, U1.1 (ADJ)
unnamed: C4.1, R3.2, R4.2, R5.2, U1.2 (VO)
unnamed: D1.2 (A), D3.1 (K), R1.2
unnamed: D2.2 (A), D4.1 (K), J2.1
unnamed: J1.1, R1.1
unnamed: J4.1, U1.3 (VI)

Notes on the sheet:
100K = 1V output
05mA --> 1V/0.005 = 200 Ohm 10mA --> 1V/0.010 = 100 Ohm 15mA --> 1V/0.015 = 67 Ohm 20mA --> 1V/0.020 = 50 Ohm (0.5mA is minimum requirement for regulation)
Dropout Voltage @ Iload = 10 mA --> 1.22V typ Dropout Voltage @ Iload = 200 mA --> 1.3V typ
2.2uF is recommendation from datasheet on output capacity to prevent oscillations
The amount of Led's depends on the supplied voltage, normal operation from PWM amplifier is 17V minus 2V due to rectifiers is 15V. For a red led a voltage of typ 1.2V is required, therfore maximum of 12 led's is achievable
BOM: 2(3)x C1,2,4 1206 multilayer ceramic capacitor 10uF 35V Fnl:1797011 1x C3 1206 multilayer ceramic capacitor 100nF 50V Fnl:1414715 2(4)x R1,2,3,4 1206 resistor Multicomp 100Ohm 500mW Fnl:2694436 1x R2 1206 resistor Multicomp 100KOhm 250mW Fnl:2073879 4x D1,2,3,4 SOD-123 Shottky rectifier 40V, 5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

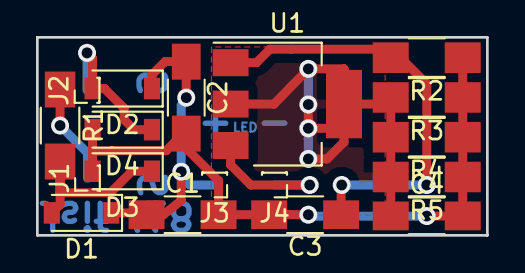
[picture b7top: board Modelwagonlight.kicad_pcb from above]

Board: 2 copper layers, 25.0 x 11.0 mm, 18 parts (0 on the bottom side), 8 nets.
